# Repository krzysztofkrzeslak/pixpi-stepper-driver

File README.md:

# pixpi-stepper-driver
Repository which holds stepper driver sources(schematic and board)for PiXPi controller <br/>

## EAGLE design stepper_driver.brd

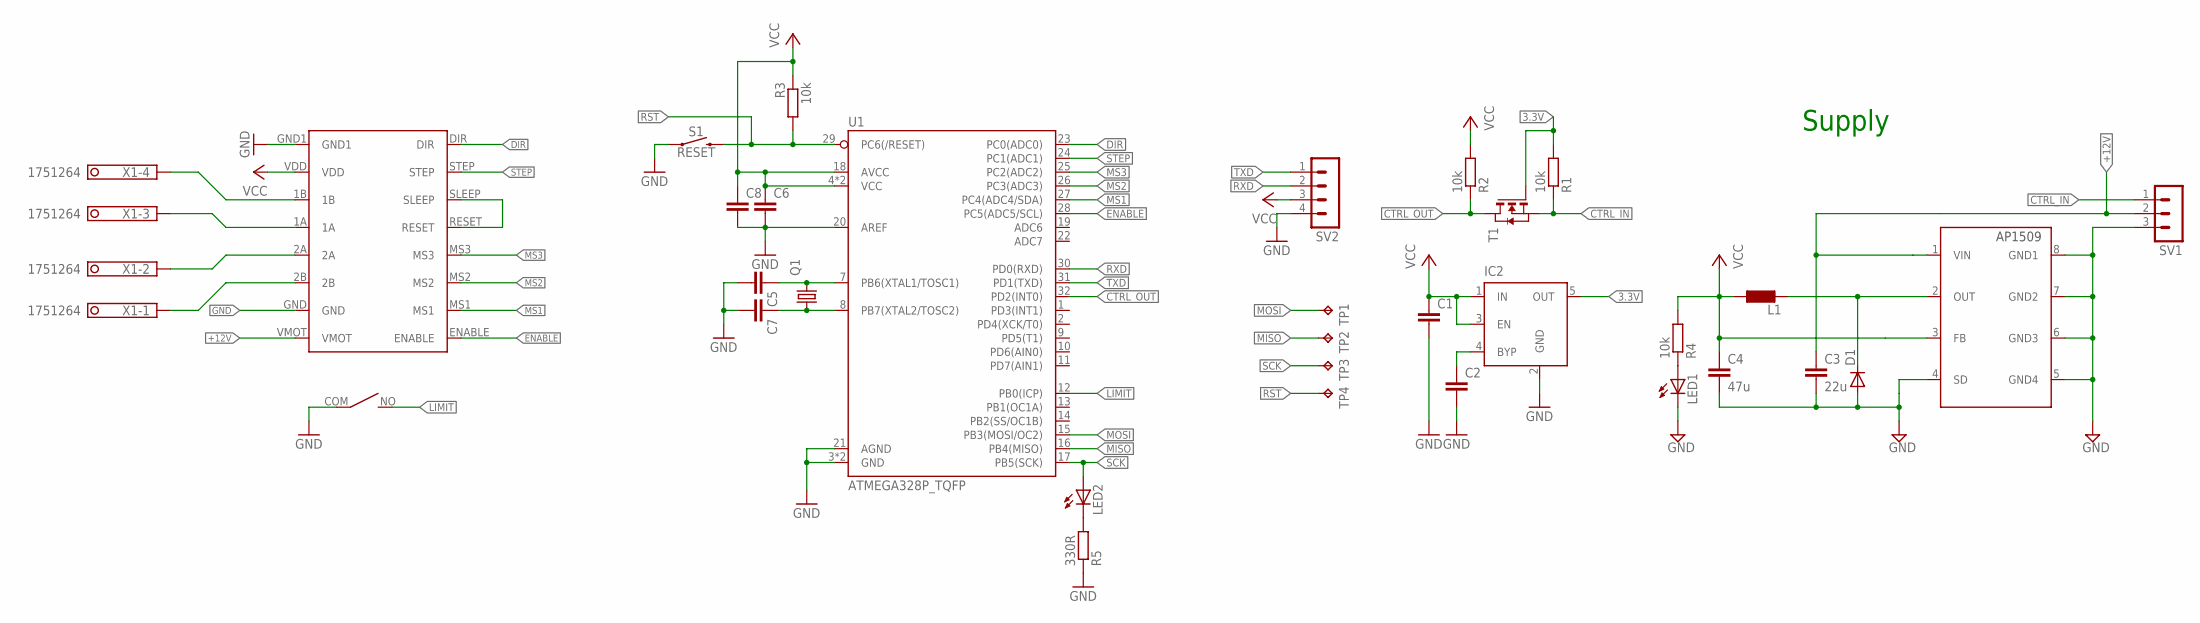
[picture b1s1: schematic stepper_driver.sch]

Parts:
C1, C2: C; C0805
C3: 22u; C1210
C4: 47u; C1210
C5, C7: C-EUC0603K; C0603K
C6, C8: C-EUC0805; C0805
D1: DIODE-SOD323-W; SOD323-W
IC2: MIC5219XX; SOT23-5
L1: LL5650M; L5650M
LED1, LED2: LEDSML0805; SML0805
Q1: KX-7; 3.2X2.5_KX-7
R1, R2, R3, R4: 10k; R0805
R5: 330R; R0805
S1: RESET; TACTILE_SWITCH_SMD_6.0X3.5MM
SV1: MA03-1
SV2: MA04-1
T1: NMOSSOT23; SOT-23
TP1, TP2, TP3, TP4: TPTP20SQ; TP20SQ
U1: ATMEGA328P_TQFP; TQFP32-08
U$1: AP1509; SOP08
U$2: A4988MODULE; A4988
U$3: D2S
X1: 1751264

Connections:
3.3V: IC2.5 (OUT), R1.2, T1.3 (G)
+12V: C3.1, SV1.2, U$1.1 (VIN), U$2.VMOT
CTRL_IN: R1.1, SV1.1, T1.2 (S)
CTRL_OUT: R2.1, T1.1 (D), U1.32 (PD2(INT0))
DIR: U1.23 (PC0(ADC0)), U$2.DIR
ENABLE: U1.28 (PC5(ADC5/SCL)), U$2.ENABLE
GND: C1.2, C2.2, C3.2, C4.2, C5.2, C6.2, C7.2, C8.2, D1.A, IC2.2 (GND), LED1.C, R5.1, S1.1, SV1.3, SV2.4, U1.3 (GND), U1.5 (GND), U1.20 (AREF), U1.21 (AGND), U$1.4 (SD), U$1.5 (GND4), U$1.6 (GND3), U$1.7 (GND2), U$1.8 (GND1), U$2.GND, U$2.GND1, U$3.COM
LIMIT: U1.12 (PB0(ICP)), U$3.NO
MISO: TP2.TP, U1.16 (PB4(MISO))
MOSI: TP1.TP, U1.15 (PB3(MOSI/OC2))
MS1: U1.27 (PC4(ADC4/SDA)), U$2.MS1
MS2: U1.26 (PC3(ADC3)), U$2.MS2
MS3: U1.25 (PC2(ADC2)), U$2.MS3
unnamed: U$2.1B, X1.4
unnamed: U$2.1A, X1.3
unnamed: U$2.RESET, U$2.SLEEP
unnamed: U$2.2A, X1.2
unnamed: U$2.2B, X1.1
unnamed: C2.1, IC2.4 (BYP)
unnamed: LED1.A, R4.1
unnamed: D1.C, L1.2, U$1.2 (OUT)
unnamed: C7.1, Q1.1, U1.8 (PB7(XTAL2/TOSC2))
unnamed: C5.1, Q1.3 (2), U1.7 (PB6(XTAL1/TOSC1))
unnamed: LED2.C, R5.2
RST: R3.2, S1.2, TP4.TP, U1.29 (PC6(/RESET))
RXD: SV2.2, U1.30 (PD0(RXD))
SCK: LED2.A, TP3.TP, U1.17 (PB5(SCK))
STEP: U1.24 (PC1(ADC1)), U$2.STEP
TXD: SV2.1, U1.31 (PD1(TXD))
VCC: C1.1, C4.1, C6.1, C8.1, IC2.1 (IN), IC2.3 (EN), L1.1, R2.2, R3.1, R4.2, SV2.3, U1.4 (VCC), U1.6 (VCC), U1.18 (AVCC), U$1.3 (FB), U$2.VDD

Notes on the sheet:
Supply

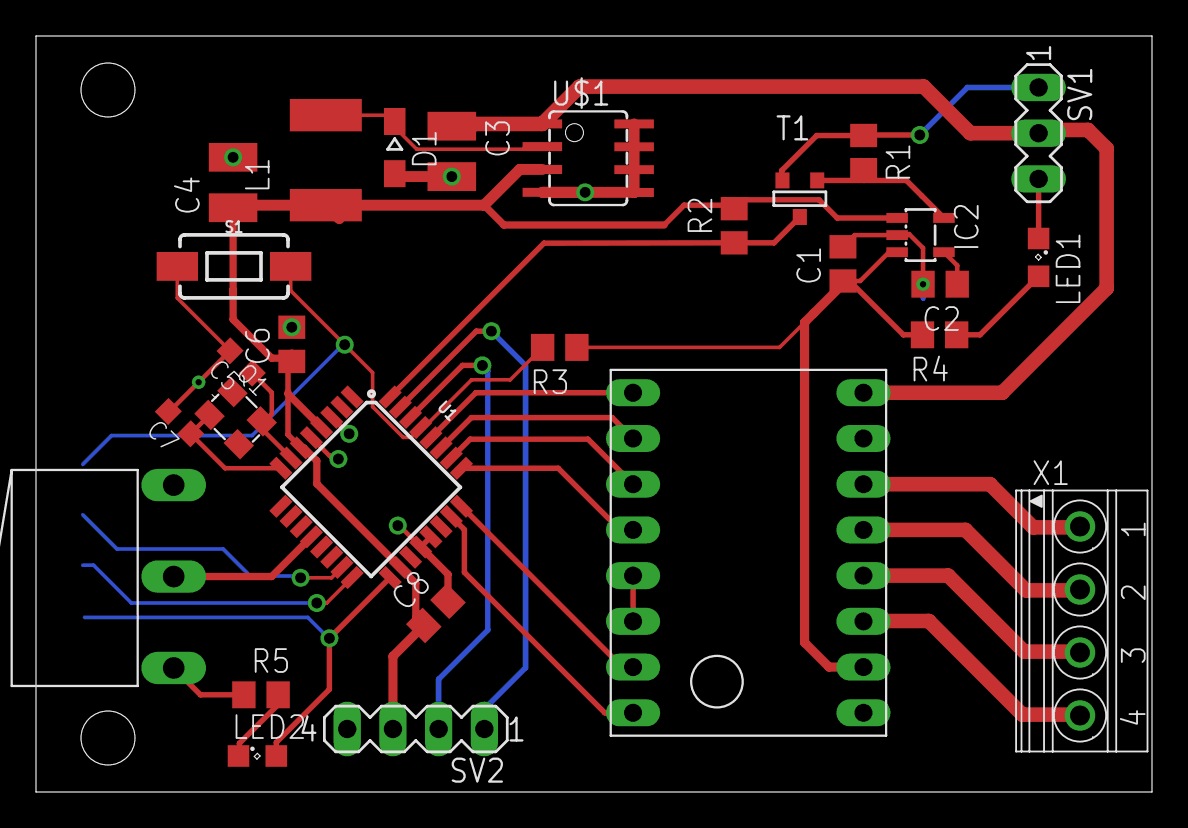
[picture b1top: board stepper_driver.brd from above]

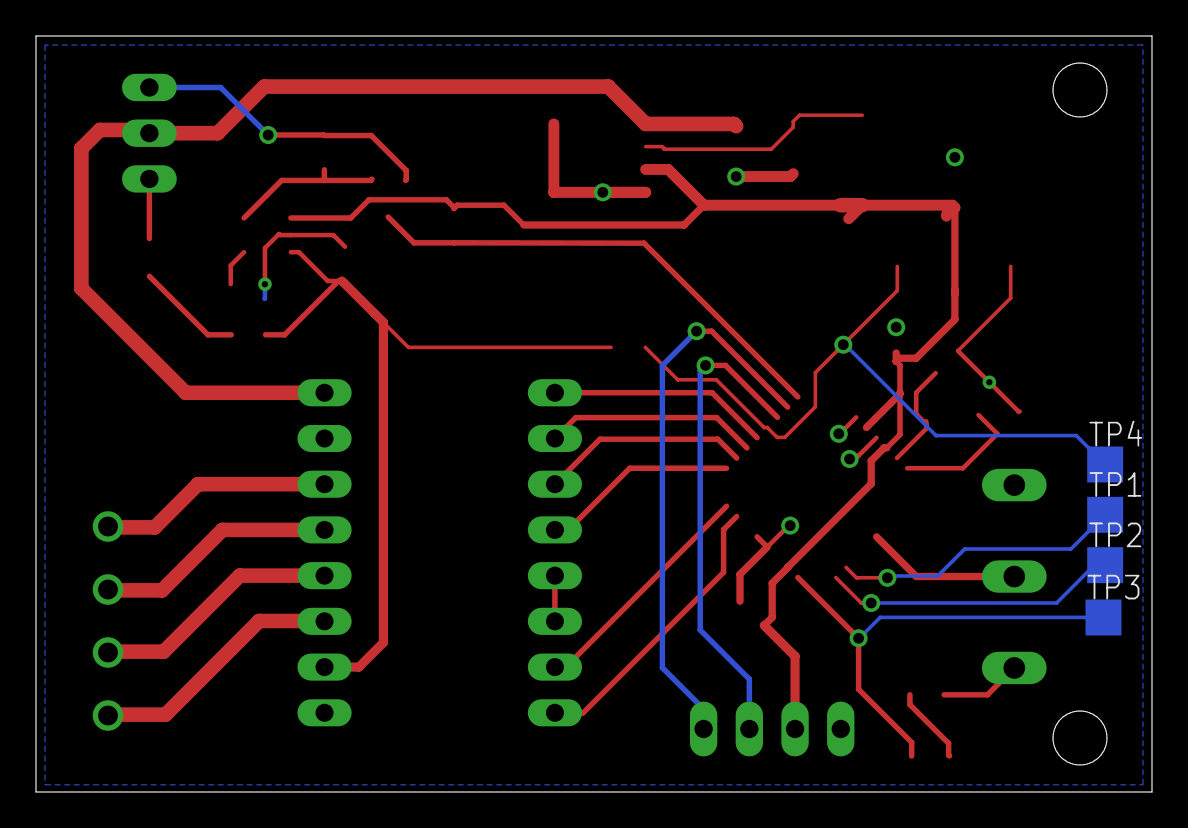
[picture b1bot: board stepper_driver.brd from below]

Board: 2 copper layers, 62.0 x 42.0 mm, 32 parts (4 on the bottom side), 30 nets.

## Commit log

2019-08-23 Added schematic, board and readme
2019-09-14 Imported MKS-SERVO42A source
2019-09-15 Changes to make it compiling
2019-09-15 changes to make it compiling#2
2019-09-18 Added possibility to control through onboard buttons: move forward, backward and enable/disable motor
2019-09-18 reduced microstepping
2019-09-18 increased maximum driving current
2019-09-18 Added "pulse" driving mode handling for driving by pixpi

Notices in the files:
parts and their libraries:
SparkFun-IC-Microcontroller: Licensing: Creative Commons ShareAlike 4.0 International - https://creativecommons.org/licenses/by-sa/4.0
crystal-geyer_V1_0: Copyright: Geyer-Electronic
